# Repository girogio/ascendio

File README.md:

# Flight Simulation Throttle Quadrant

This project is aimed at creating a throttle quadrant for flight simulation.
Based on an Arduino Nano, and motorized slider potentiometers (like the one
found in A/V mixers) we shall emulate the different detents and mechanical
resistance of the various levers found in a real aircraft.

I plan to support the throttle behaviour of the following aircrafts:

- Airbus A320-200
- Boeing 737

## Hardware

The hardware is based on the following components:

| Quantity | Component                                                                                                      | Description                                                                                                   |
| -------- | -------------------------------------------------------------------------------------------------------------- | ------------------------------------------------------------------------------------------------------------- |
| 1        | Teensy 3.2                                                                                                     | Microcontroller board                                                                                         |
| 4        | [Motorized Slider Potentiometer](https://tech.alpsalpine.com/e/products/detail/RSA0N11M9A0K/)                  | Alps RSA0N11M9A0K                                                                                             |
| 2        | [Lever Switch](https://www.fabian.com.mt/en/products/webshop/19924/switch-toggle-miniature-spdt-on-off-on.htm) | Engine start switches                                                                                         |
| 1        | [3 position rotary switch](https://www.fabian.com.mt/en/products/webshop/9117/switch-rotary-3p-4w-bbm.htm)                                                                                       | Engine MODE selector switch |
| 4        | [TA7219SG](https://www.alldatasheet.com/datasheet-pdf/pdf/215391/TOSHIBA/TA7291SG.html)                                                                      | Dual full H-bridge motor driver for potentiometers                                                            |

> [!NOTE]
> The project is still in the design phase, and the components listed above are subject to change.

## Software

The software for this projcet is split into two parts:

- The firmware running on the Teensy 3.2
- The software running on the host computer to interface with the Arduino Nano and the flight simulator

## Dependencies

- [clang](https://rust-lang.github.io/rust-bindgen/requirements.html)
- [SimConnect SDK]()

## License

This project is licensed under the GNU General Public License v3.0. See the
[LICENSE](LICENSE) file for more information.

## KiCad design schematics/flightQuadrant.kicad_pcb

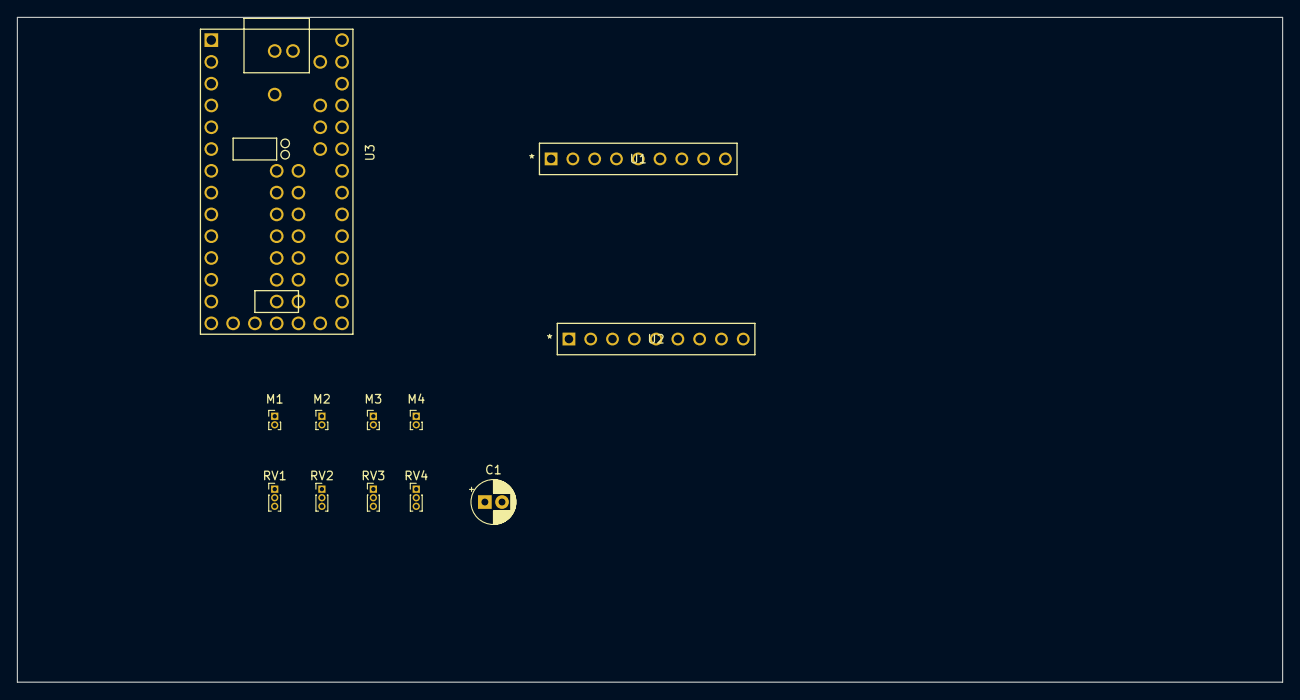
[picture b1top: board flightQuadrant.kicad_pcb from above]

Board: 2 copper layers, 147.5 x 77.5 mm, 12 parts (0 on the bottom side), 2 nets, no tracks yet.

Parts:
C1: 100nF; CP_Radial_D5.0mm_P2.00mm
M1: M_ENG1; PinHeader_1x02_P1.00mm_Vertical
M2: M_ENG2; PinHeader_1x02_P1.00mm_Vertical
M3: M_BRK; PinHeader_1x02_P1.00mm_Vertical
M4: M_FLP; PinHeader_1x02_P1.00mm_Vertical
RV1: R_ENG1; PinHeader_1x03_P1.00mm_Vertical
RV2: R_ENG2; PinHeader_1x03_P1.00mm_Vertical
RV3: R_BRK; PinHeader_1x03_P1.00mm_Vertical
RV4: R_FLP; PinHeader_1x03_P1.00mm_Vertical
U1, U2: ta7291sgo; SIP9_TOS
U3: Teensy3.2; Teensy30_31_32_All_Pins

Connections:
unnamed: C1.1, RV1.3, RV2.3, RV3.3, RV4.3
unnamed: C1.2, RV1.1, RV2.1, RV3.1, RV4.1

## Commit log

2025-01-27 Added .gitignore, readme and license
2025-01-27 Added arduino sketch
2025-01-27 Added initial tauri project and test rust app
2025-01-27 Updated .gitignore
2025-01-27 Added kicad project
2025-01-27 Fixed npm build on windows
2025-01-27 Organized arduino code in classes for scalability
2025-01-27 Removed target folder
2025-01-27 Migrate to teeensyyyy 3.2
2025-02-09 Much needed changes across the board
2025-02-09 Update arduino code firmware!
2025-02-09 Reverted to clean tauri ui project
2025-02-09 Removed .vscodes
2025-02-09 setup frontend basics
2025-02-09 prevented image dragging
2025-02-09 added status bar
2025-02-09 implemented status bar
2025-02-09 fixed name in package.json
2025-02-09 fixed capabilities to enable window controls and events
2025-02-09 added title bar
2025-02-09 fixed inconsistent padding
2025-02-09 added basic routes
2025-02-09 added navbar
2025-02-09 changed look of navbar
2025-02-10 Build script moves dll automatically
2025-02-12 MCU connection and disconnection works
2025-02-12 added button component
2025-02-12 moved window controls
2025-02-12 changed button colour
2025-02-12 added connect button
2025-02-12 removed unused imports
2025-02-12 fixed text change for connect button
2025-03-02 switched to platform io
